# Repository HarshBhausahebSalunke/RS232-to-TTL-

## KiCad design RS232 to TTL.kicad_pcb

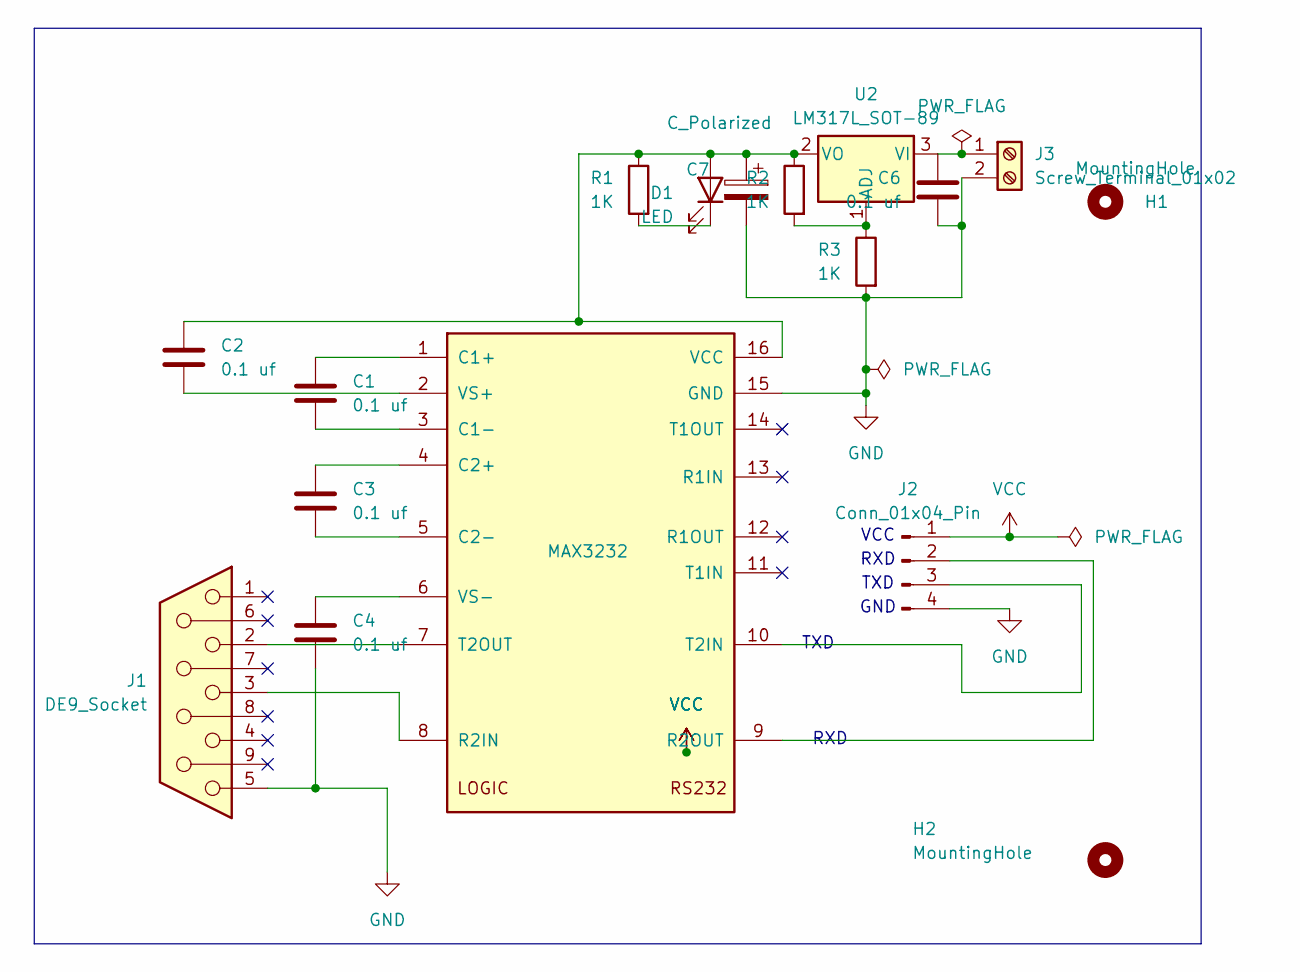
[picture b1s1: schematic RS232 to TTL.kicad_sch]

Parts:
C1, C2, C3, C4, C6: 0.1 uf; C_0805_2012Metric
C7: C_Polarized; CP_EIA-3216-18_Kemet-A
D1: LED; LED_0805_2012Metric
H1, H2: MountingHole; MountingHole_3.2mm_M3
J1: DE9_Socket; DSUB-9_Socket_Horizontal_P2.77x2.84mm_EdgePinOffset9.40mm
J2: Conn_01x04_Pin; PinHeader_1x04_P2.54mm_Vertical
J3: Screw_Terminal_01x02; TerminalBlock_4Ucon_1x02_P3.50mm_Horizontal
R1, R2, R3: 1K; R_0805_2012Metric
U1: MAX3232; SOIC-16_3.9x9.9mm_P1.27mm
U2: LM317L_SOT-89; SOT-89-3

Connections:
GND: C4.2, C6.2, C7.2, J1.5, J2.4, J3.2, R3.2, U1.15 (GND)
unnamed: C2.1, C7.1, D1.2 (A), R1.1, R2.1, U1.16 (VCC), U2.2 (VO)
unnamed: D1.1 (K), R1.2
unnamed: J2.2, U1.9 (R2OUT)
unnamed: J2.3, U1.10 (T2IN)
unnamed: C6.1, J3.1, U2.3 (VI)
unnamed: C1.2, U1.1 (C1+)
unnamed: C1.1, U1.3 (C1-)
unnamed: C3.2, U1.4 (C2+)
unnamed: C3.1, U1.5 (C2-)
unnamed: J1.3, U1.8 (R2IN)
unnamed: J1.2, U1.7 (T2OUT)
unnamed: C2.2, U1.2 (VS+)
unnamed: C4.1, U1.6 (VS-)
unnamed: R2.2, R3.1, U2.1 (ADJ)
VCC: J2.1

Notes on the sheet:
GND
RXD
TXD
TXD
VCC

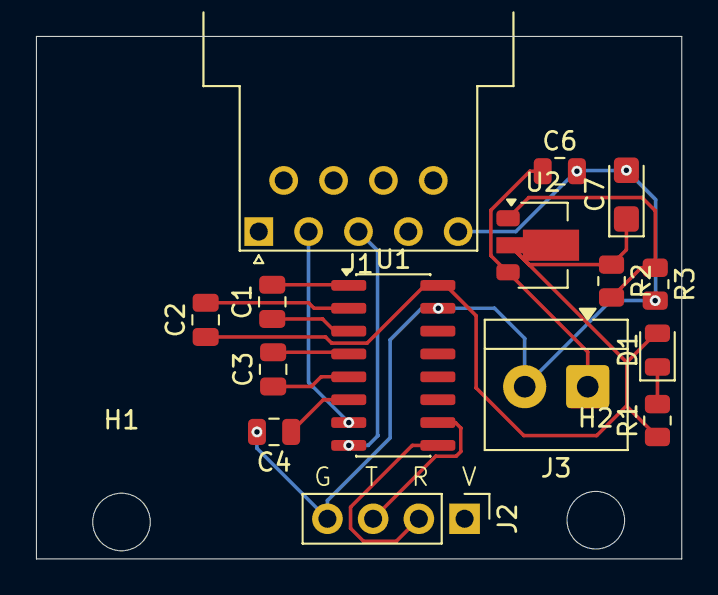
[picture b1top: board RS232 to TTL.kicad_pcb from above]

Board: 2 copper layers, 35.9 x 29.0 mm, 17 parts (0 on the bottom side), 15 nets.
